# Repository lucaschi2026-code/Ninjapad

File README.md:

# Ninjapad
Ninjapad is a macropad with 9 keys, 1 rotary encoder, and an 0.91 inch OLED display. It uses a custom PCB, 3D printed case, and QMK firmware. OLED features different animations inspired by Naruto.

[🎬Build Montage🎬](https://www.youtube.com/shorts/z15oCYiYoOs)

[🎬Showcase Edit🎬](https://www.youtube.com/shorts/6WCUAFyBArM)

[🎬Full Build + Demo🎬](https://www.youtube.com/watch?v=4l7bW2d6SSs)

## Features

- 9 key + rotary encoder layout
- [3D printed case](/Production)
- [3D printed rotary knob](/Production/Rotary_Keycap.step)
- [Custom PCB](/PCB)
- 128x32 OLED Display
- [QMK firmware (keys, rotary encoder, OLED can be programmed to anything)](/Firmware)
- 🎬Naruto inspired animations🎬

https://github.com/user-attachments/assets/e3caf68b-d00f-4336-b8fd-c6721da46e56

## Schematic

- Features a matrix to save pins and diodes to prevent ghosting.

## PCB

- Features 2 vias and flipped diodes so that they attach under the PCB.

## Case Components
Top Shell:

- 4 through holes to secure to bottom shell. Underside features 4 insert pockets for heat set inserts to secure PCB. 

Bottom Shell:

- 4 insert pockets and a cutout for USB cable.

The shells are attached with the top over the bottom. The shells are secured with 4 M3x16mm screws through heat set inserts on the bottom shell.
## BOM
| Item | Qty |
|------|-----|
| Seeed XIAO RP2040 | 1 |
| Through-hole 1N4148 Diode | 9 |
| MX-Style Switch | 9 |
| EC11 Rotary Encoder | 1 |
| 0.91 inch OLED Display | 1 |
| White Blank DSA Keycap | 9 |
| M3x16mm Screw | 4 |
| M3x5mmx4mm Heatset Insert | 8 |
| M3x5mm Screw | 4 |
| Case (top and bottom shell) | 1 |
| Custom PCB | 1 |

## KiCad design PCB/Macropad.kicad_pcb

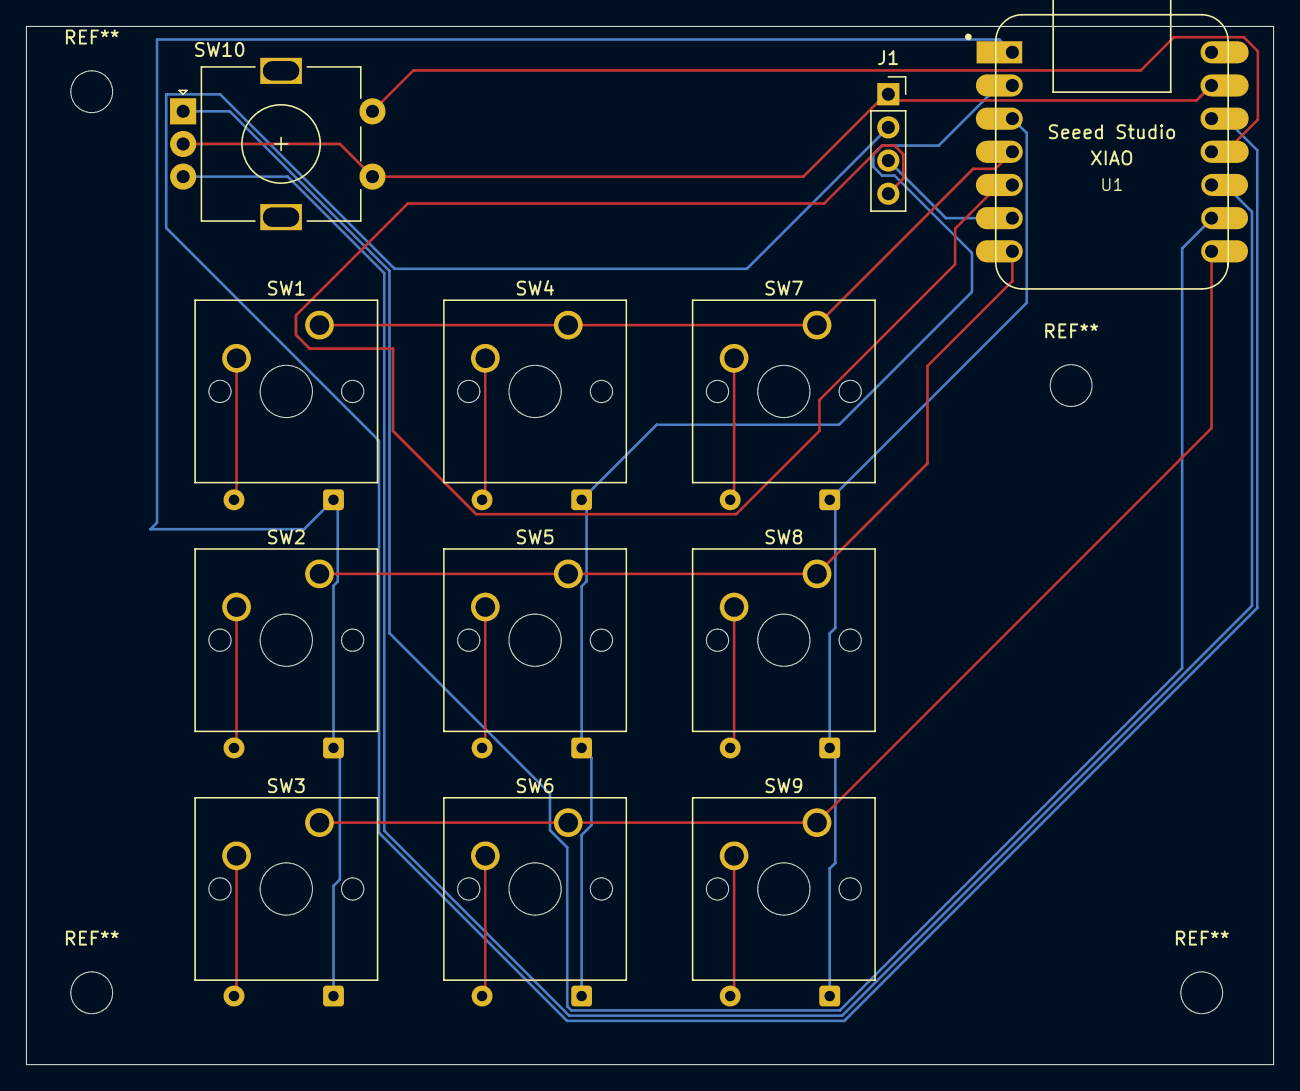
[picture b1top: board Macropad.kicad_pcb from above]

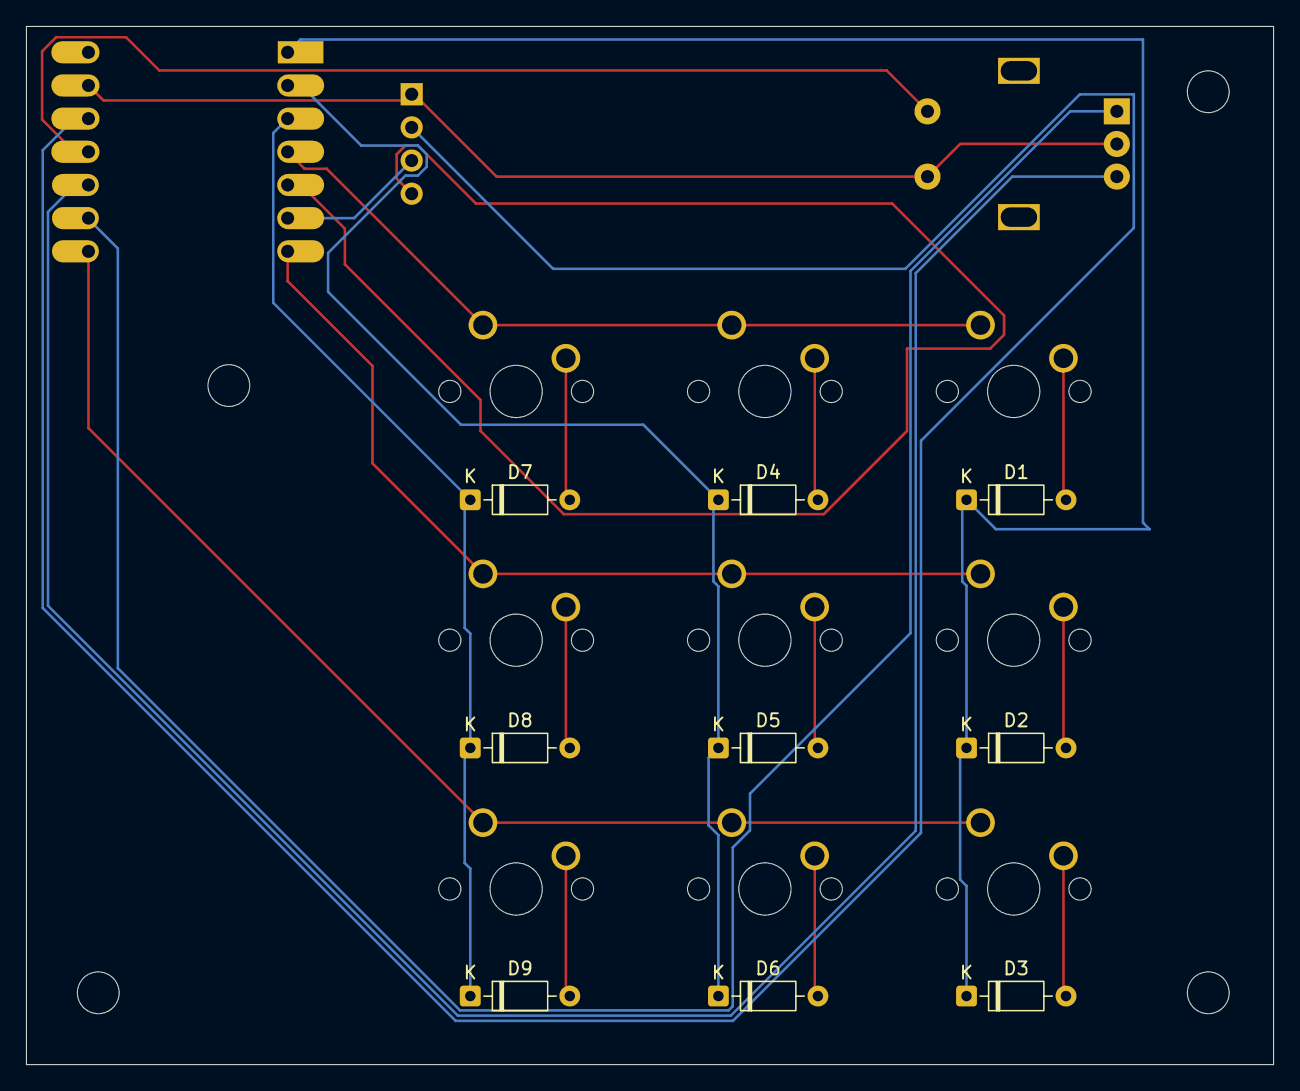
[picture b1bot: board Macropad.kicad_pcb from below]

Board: 2 copper layers, 95.5 x 79.5 mm, 21 parts (9 on the bottom side), 22 nets.

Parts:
D1, D2, D3, D4, D5, D6, D7, D8, D9: 1N4148; D_DO-35_SOD27_P7.62mm_Horizontal
J1: Conn_01x04_Pin; PinSocket_1x04_P2.54mm_Vertical
SW1, SW2, SW3, SW4, SW5, SW6, SW7, SW8, SW9: SW_Push; SW_Cherry_MX_1.00u_PCB
SW10: RotaryEncoder_Switch; RotaryEncoder_Alps_EC11E-Switch_Vertical_H20mm
U1: MOUDLE-SEEEDUINO-XIAO; XIAO-Generic-Hybrid-14P-2.54-21X17.8MM

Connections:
/3V3: J1.2, U1.12 (3V3)
/Col 1: SW1.1, SW4.1, SW7.1, U1.4 (PA11_A3_D3)
/Col 2: SW2.1, SW5.1, SW8.1, U1.7 (PB08_A6_D6_TX)
/Col 3: SW3.1, SW6.1, SW9.1, U1.8 (PB09_A7_D7_RX)
/ENC_A: SW10.A, U1.9 (PA7_A8_D8_SCK)
/ENC_B: SW10.B, U1.10 (PA5_A9_D9_MISO)
/ENC_SW: SW10.S2, U1.11 (PA6_A10_D10_MOSI)
/Row 1: D1.1 (K), D2.1 (K), D3.1 (K), U1.1 (PA02_A0_D0)
/Row 2: D4.1 (K), D5.1 (K), D6.1 (K), U1.2 (PA4_A1_D1)
/Row 3: D7.1 (K), D8.1 (K), D9.1 (K), U1.3 (PA10_A2_D2)
/SCL: J1.3, U1.6 (PA9_A5_D5_SCL)
/SDA: J1.4, U1.5 (PA8_A4_D4_SDA)
GND: J1.1, SW10.C, SW10.S1, U1.13 (GND)
unnamed: D1.2 (A), SW1.2
unnamed: D2.2 (A), SW2.2
unnamed: D3.2 (A), SW3.2
unnamed: D4.2 (A), SW4.2
unnamed: D5.2 (A), SW5.2
unnamed: D6.2 (A), SW6.2
unnamed: D7.2 (A), SW7.2
unnamed: D8.2 (A), SW8.2
unnamed: D9.2 (A), SW9.2
